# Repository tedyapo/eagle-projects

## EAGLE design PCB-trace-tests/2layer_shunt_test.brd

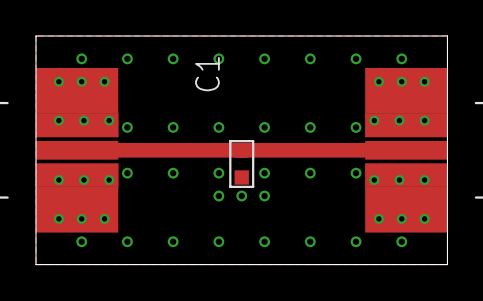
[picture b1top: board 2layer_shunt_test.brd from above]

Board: 2 copper layers, 22.9 x 12.7 mm, 3 parts (0 on the bottom side), 2 nets.

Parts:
C1: C0603
J1, J2: SMA_EDGE_LAUNCH_2L

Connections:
GND: C1.P$1, J1.BOTTOM_GND, J1.GND@1, J1.GND@2, J1.GND@3, J1.GND@4, J1.GND@5, J1.GND@6, J1.GND@7, J1.GND@8, J1.GND@11, J1.GND@12, J1.GND@14, J1.GND@15, J1.GND@16, J1.GND@17, J1.GND_PAD1, J1.GND_PAD2, J2.BOTTOM_GND, J2.GND@1, J2.GND@2, J2.GND@3, J2.GND@4, J2.GND@5, J2.GND@6, J2.GND@7, J2.GND@8, J2.GND@11, J2.GND@12, J2.GND@14, J2.GND@15, J2.GND@16, J2.GND@17, J2.GND_PAD1, J2.GND_PAD2
unnamed: C1.P$2, J1.CENTER@1, J2.CENTER@1

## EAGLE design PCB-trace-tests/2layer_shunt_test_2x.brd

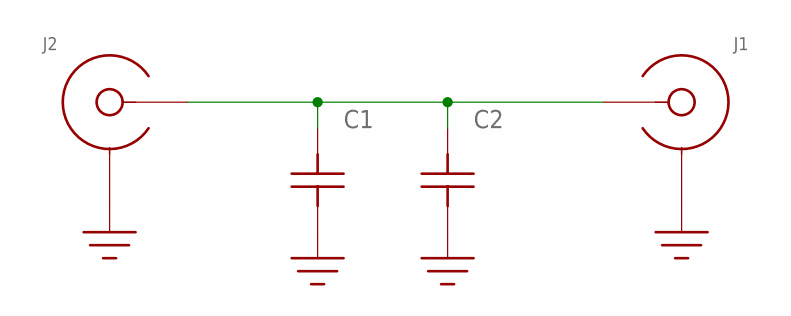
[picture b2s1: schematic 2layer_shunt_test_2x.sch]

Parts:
C1: C0603
C2: C; C0402
J1, J2: SMA_END_LAUNCH2L; SMA_EDGE_LAUNCH_2L

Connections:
GND: C1.P$1, C2.1, J1.BOTTOM_GND (SHIELD), J1.GND@1 (SHIELD), J1.GND@2 (SHIELD), J1.GND@3 (SHIELD), J1.GND@4 (SHIELD), J1.GND@5 (SHIELD), J1.GND@6 (SHIELD), J1.GND@7 (SHIELD), J1.GND@8 (SHIELD), J1.GND@11 (SHIELD), J1.GND@12 (SHIELD), J1.GND@14 (SHIELD), J1.GND@15 (SHIELD), J1.GND@16 (SHIELD), J1.GND@17 (SHIELD), J1.GND_PAD1 (SHIELD), J1.GND_PAD2 (SHIELD), J2.BOTTOM_GND (SHIELD), J2.GND@1 (SHIELD), J2.GND@2 (SHIELD), J2.GND@3 (SHIELD), J2.GND@4 (SHIELD), J2.GND@5 (SHIELD), J2.GND@6 (SHIELD), J2.GND@7 (SHIELD), J2.GND@8 (SHIELD), J2.GND@11 (SHIELD), J2.GND@12 (SHIELD), J2.GND@14 (SHIELD), J2.GND@15 (SHIELD), J2.GND@16 (SHIELD), J2.GND@17 (SHIELD), J2.GND_PAD1 (SHIELD), J2.GND_PAD2 (SHIELD)
unnamed: C1.P$2, C2.2, J1.CENTER@1 (CENTER), J2.CENTER@1 (CENTER)

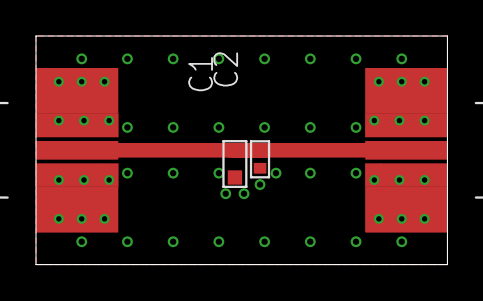
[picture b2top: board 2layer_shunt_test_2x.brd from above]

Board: 2 copper layers, 22.9 x 12.7 mm, 4 parts (0 on the bottom side), 2 nets.

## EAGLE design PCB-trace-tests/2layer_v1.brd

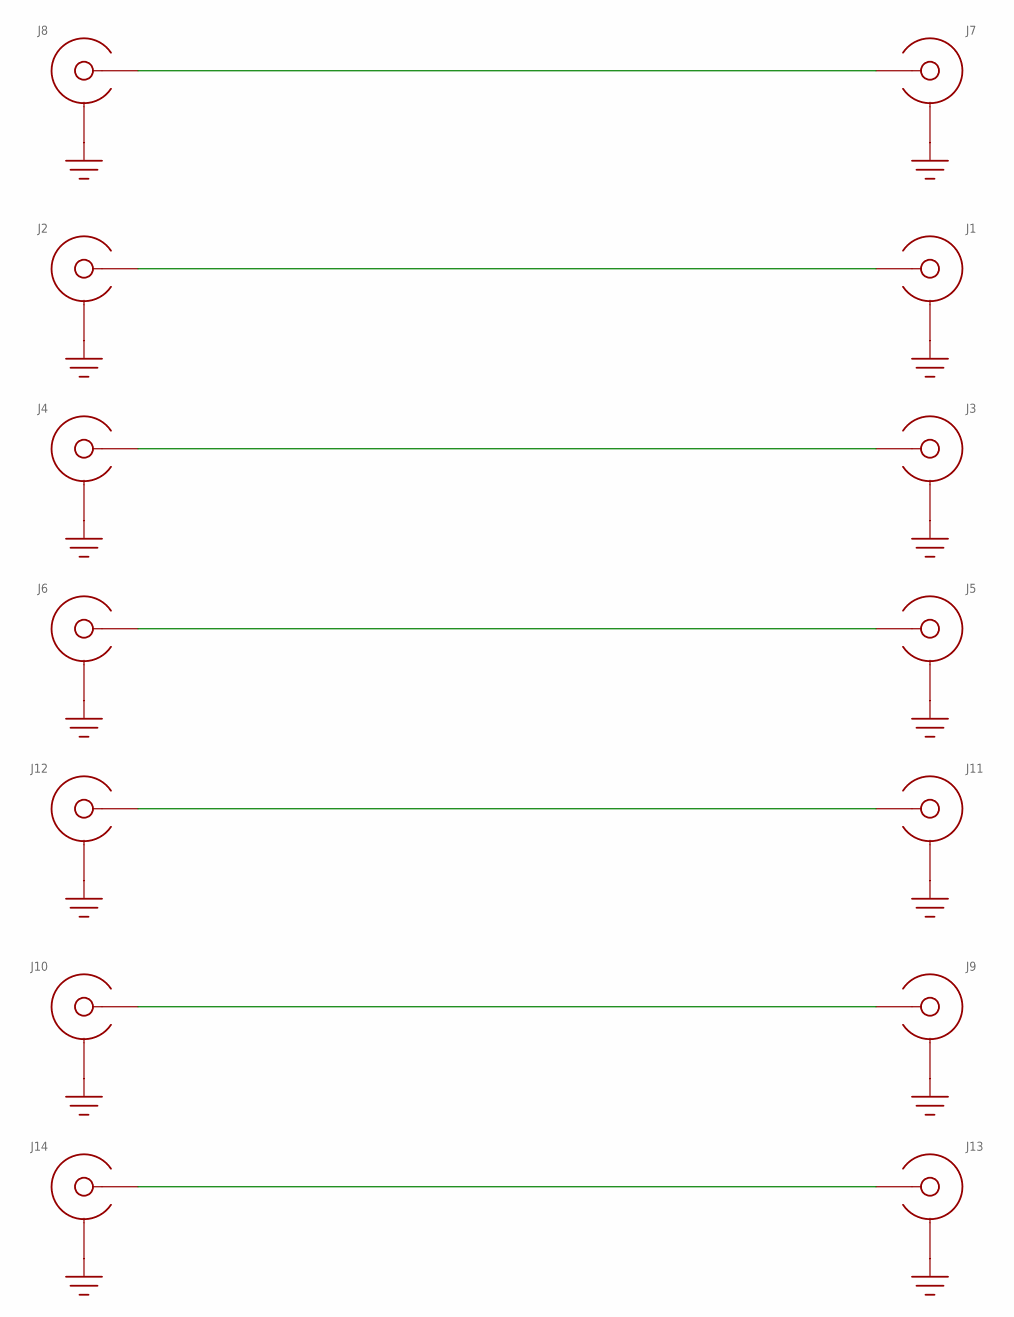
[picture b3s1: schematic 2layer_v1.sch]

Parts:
J1, J2, J3, J4, J5, J6, J7, J8, J9, J10, J11, J12, J13, J14: SMA_END_LAUNCH2L; SMA_EDGE_LAUNCH_2L

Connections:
GND: J1.BOTTOM_GND (SHIELD), J1.GND@1 (SHIELD), J1.GND@2 (SHIELD), J1.GND@3 (SHIELD), J1.GND@4 (SHIELD), J1.GND@5 (SHIELD), J1.GND@6 (SHIELD), J1.GND@7 (SHIELD), J1.GND@8 (SHIELD), J1.GND@11 (SHIELD), J1.GND@12 (SHIELD), J1.GND@14 (SHIELD), J1.GND@15 (SHIELD), J1.GND@16 (SHIELD), J1.GND@17 (SHIELD), J1.GND_PAD1 (SHIELD), J1.GND_PAD2 (SHIELD), J2.BOTTOM_GND (SHIELD), J2.GND@1 (SHIELD), J2.GND@2 (SHIELD), J2.GND@3 (SHIELD), J2.GND@4 (SHIELD), J2.GND@5 (SHIELD), J2.GND@6 (SHIELD), J2.GND@7 (SHIELD), J2.GND@8 (SHIELD), J2.GND@11 (SHIELD), J2.GND@12 (SHIELD), J2.GND@14 (SHIELD), J2.GND@15 (SHIELD), J2.GND@16 (SHIELD), J2.GND@17 (SHIELD), J2.GND_PAD1 (SHIELD), J2.GND_PAD2 (SHIELD), J3.BOTTOM_GND (SHIELD), J3.GND@1 (SHIELD), J3.GND@2 (SHIELD), J3.GND@3 (SHIELD), J3.GND@4 (SHIELD), J3.GND@5 (SHIELD), J3.GND@6 (SHIELD), J3.GND@7 (SHIELD), J3.GND@8 (SHIELD), J3.GND@11 (SHIELD), J3.GND@12 (SHIELD), J3.GND@14 (SHIELD), J3.GND@15 (SHIELD), J3.GND@16 (SHIELD), J3.GND@17 (SHIELD), J3.GND_PAD1 (SHIELD), J3.GND_PAD2 (SHIELD), J4.BOTTOM_GND (SHIELD), J4.GND@1 (SHIELD), J4.GND@2 (SHIELD), J4.GND@3 (SHIELD), J4.GND@4 (SHIELD), J4.GND@5 (SHIELD), J4.GND@6 (SHIELD), J4.GND@7 (SHIELD), J4.GND@8 (SHIELD), J4.GND@11 (SHIELD), J4.GND@12 (SHIELD), J4.GND@14 (SHIELD), J4.GND@15 (SHIELD), J4.GND@16 (SHIELD), J4.GND@17 (SHIELD), J4.GND_PAD1 (SHIELD), J4.GND_PAD2 (SHIELD), J5.BOTTOM_GND (SHIELD), J5.GND@1 (SHIELD), J5.GND@2 (SHIELD), J5.GND@3 (SHIELD), J5.GND@4 (SHIELD), J5.GND@5 (SHIELD), J5.GND@6 (SHIELD), J5.GND@7 (SHIELD), J5.GND@8 (SHIELD), J5.GND@11 (SHIELD), J5.GND@12 (SHIELD), J5.GND@14 (SHIELD), J5.GND@15 (SHIELD), J5.GND@16 (SHIELD), J5.GND@17 (SHIELD), J5.GND_PAD1 (SHIELD), J5.GND_PAD2 (SHIELD), J6.BOTTOM_GND (SHIELD), J6.GND@1 (SHIELD), J6.GND@2 (SHIELD), J6.GND@3 (SHIELD), J6.GND@4 (SHIELD), J6.GND@5 (SHIELD), J6.GND@6 (SHIELD), J6.GND@7 (SHIELD), J6.GND@8 (SHIELD), J6.GND@11 (SHIELD), J6.GND@12 (SHIELD), J6.GND@14 (SHIELD), J6.GND@15 (SHIELD), J6.GND@16 (SHIELD), J6.GND@17 (SHIELD), J6.GND_PAD1 (SHIELD), J6.GND_PAD2 (SHIELD), J7.BOTTOM_GND (SHIELD), J7.GND@1 (SHIELD), J7.GND@2 (SHIELD), J7.GND@3 (SHIELD), J7.GND@4 (SHIELD), J7.GND@5 (SHIELD), J7.GND@6 (SHIELD), J7.GND@7 (SHIELD), J7.GND@8 (SHIELD), J7.GND@11 (SHIELD), J7.GND@12 (SHIELD), J7.GND@14 (SHIELD), J7.GND@15 (SHIELD), J7.GND@16 (SHIELD), J7.GND@17 (SHIELD), J7.GND_PAD1 (SHIELD), J7.GND_PAD2 (SHIELD), J8.BOTTOM_GND (SHIELD), J8.GND@1 (SHIELD), J8.GND@2 (SHIELD), J8.GND@3 (SHIELD), J8.GND@4 (SHIELD), J8.GND@5 (SHIELD), J8.GND@6 (SHIELD), J8.GND@7 (SHIELD), J8.GND@8 (SHIELD), J8.GND@11 (SHIELD), J8.GND@12 (SHIELD), J8.GND@14 (SHIELD), J8.GND@15 (SHIELD), J8.GND@16 (SHIELD), J8.GND@17 (SHIELD), J8.GND_PAD1 (SHIELD), J8.GND_PAD2 (SHIELD), J9.BOTTOM_GND (SHIELD), J9.GND@1 (SHIELD), J9.GND@2 (SHIELD), J9.GND@3 (SHIELD), J9.GND@4 (SHIELD), J9.GND@5 (SHIELD), J9.GND@6 (SHIELD), J9.GND@7 (SHIELD), J9.GND@8 (SHIELD), J9.GND@11 (SHIELD), J9.GND@12 (SHIELD), J9.GND@14 (SHIELD), J9.GND@15 (SHIELD), J9.GND@16 (SHIELD), J9.GND@17 (SHIELD), J9.GND_PAD1 (SHIELD), J9.GND_PAD2 (SHIELD), J10.BOTTOM_GND (SHIELD), J10.GND@1 (SHIELD), J10.GND@2 (SHIELD), J10.GND@3 (SHIELD), J10.GND@4 (SHIELD), J10.GND@5 (SHIELD), J10.GND@6 (SHIELD), J10.GND@7 (SHIELD), J10.GND@8 (SHIELD), J10.GND@11 (SHIELD), J10.GND@12 (SHIELD), J10.GND@14 (SHIELD), J10.GND@15 (SHIELD), J10.GND@16 (SHIELD), J10.GND@17 (SHIELD), J10.GND_PAD1 (SHIELD), J10.GND_PAD2 (SHIELD), J11.BOTTOM_GND (SHIELD), J11.GND@1 (SHIELD), J11.GND@2 (SHIELD), J11.GND@3 (SHIELD), J11.GND@4 (SHIELD), J11.GND@5 (SHIELD), J11.GND@6 (SHIELD), J11.GND@7 (SHIELD), J11.GND@8 (SHIELD), J11.GND@11 (SHIELD), J11.GND@12 (SHIELD), J11.GND@14 (SHIELD), J11.GND@15 (SHIELD), J11.GND@16 (SHIELD), J11.GND@17 (SHIELD), J11.GND_PAD1 (SHIELD), J11.GND_PAD2 (SHIELD), J12.BOTTOM_GND (SHIELD), J12.GND@1 (SHIELD), J12.GND@2 (SHIELD), J12.GND@3 (SHIELD), J12.GND@4 (SHIELD), J12.GND@5 (SHIELD), J12.GND@6 (SHIELD), J12.GND@7 (SHIELD), J12.GND@8 (SHIELD), J12.GND@11 (SHIELD), J12.GND@12 (SHIELD), J12.GND@14 (SHIELD), J12.GND@15 (SHIELD), J12.GND@16 (SHIELD), J12.GND@17 (SHIELD), J12.GND_PAD1 (SHIELD), J12.GND_PAD2 (SHIELD), J13.BOTTOM_GND (SHIELD), J13.GND@1 (SHIELD), J13.GND@2 (SHIELD), J13.GND@3 (SHIELD), J13.GND@4 (SHIELD), J13.GND@5 (SHIELD), J13.GND@6 (SHIELD), J13.GND@7 (SHIELD), J13.GND@8 (SHIELD), J13.GND@11 (SHIELD), J13.GND@12 (SHIELD), J13.GND@14 (SHIELD), J13.GND@15 (SHIELD), J13.GND@16 (SHIELD), J13.GND@17 (SHIELD), J13.GND_PAD1 (SHIELD), J13.GND_PAD2 (SHIELD), J14.BOTTOM_GND (SHIELD), J14.GND@1 (SHIELD), J14.GND@2 (SHIELD), J14.GND@3 (SHIELD), J14.GND@4 (SHIELD), J14.GND@5 (SHIELD), J14.GND@6 (SHIELD), J14.GND@7 (SHIELD), J14.GND@8 (SHIELD), J14.GND@11 (SHIELD), J14.GND@12 (SHIELD), J14.GND@14 (SHIELD), J14.GND@15 (SHIELD), J14.GND@16 (SHIELD), J14.GND@17 (SHIELD), J14.GND_PAD1 (SHIELD), J14.GND_PAD2 (SHIELD)
unnamed: J1.CENTER@1 (CENTER), J2.CENTER@1 (CENTER)
unnamed: J3.CENTER@1 (CENTER), J4.CENTER@1 (CENTER)
unnamed: J5.CENTER@1 (CENTER), J6.CENTER@1 (CENTER)
unnamed: J7.CENTER@1 (CENTER), J8.CENTER@1 (CENTER)
unnamed: J9.CENTER@1 (CENTER), J10.CENTER@1 (CENTER)
unnamed: J11.CENTER@1 (CENTER), J12.CENTER@1 (CENTER)
unnamed: J13.CENTER@1 (CENTER), J14.CENTER@1 (CENTER)

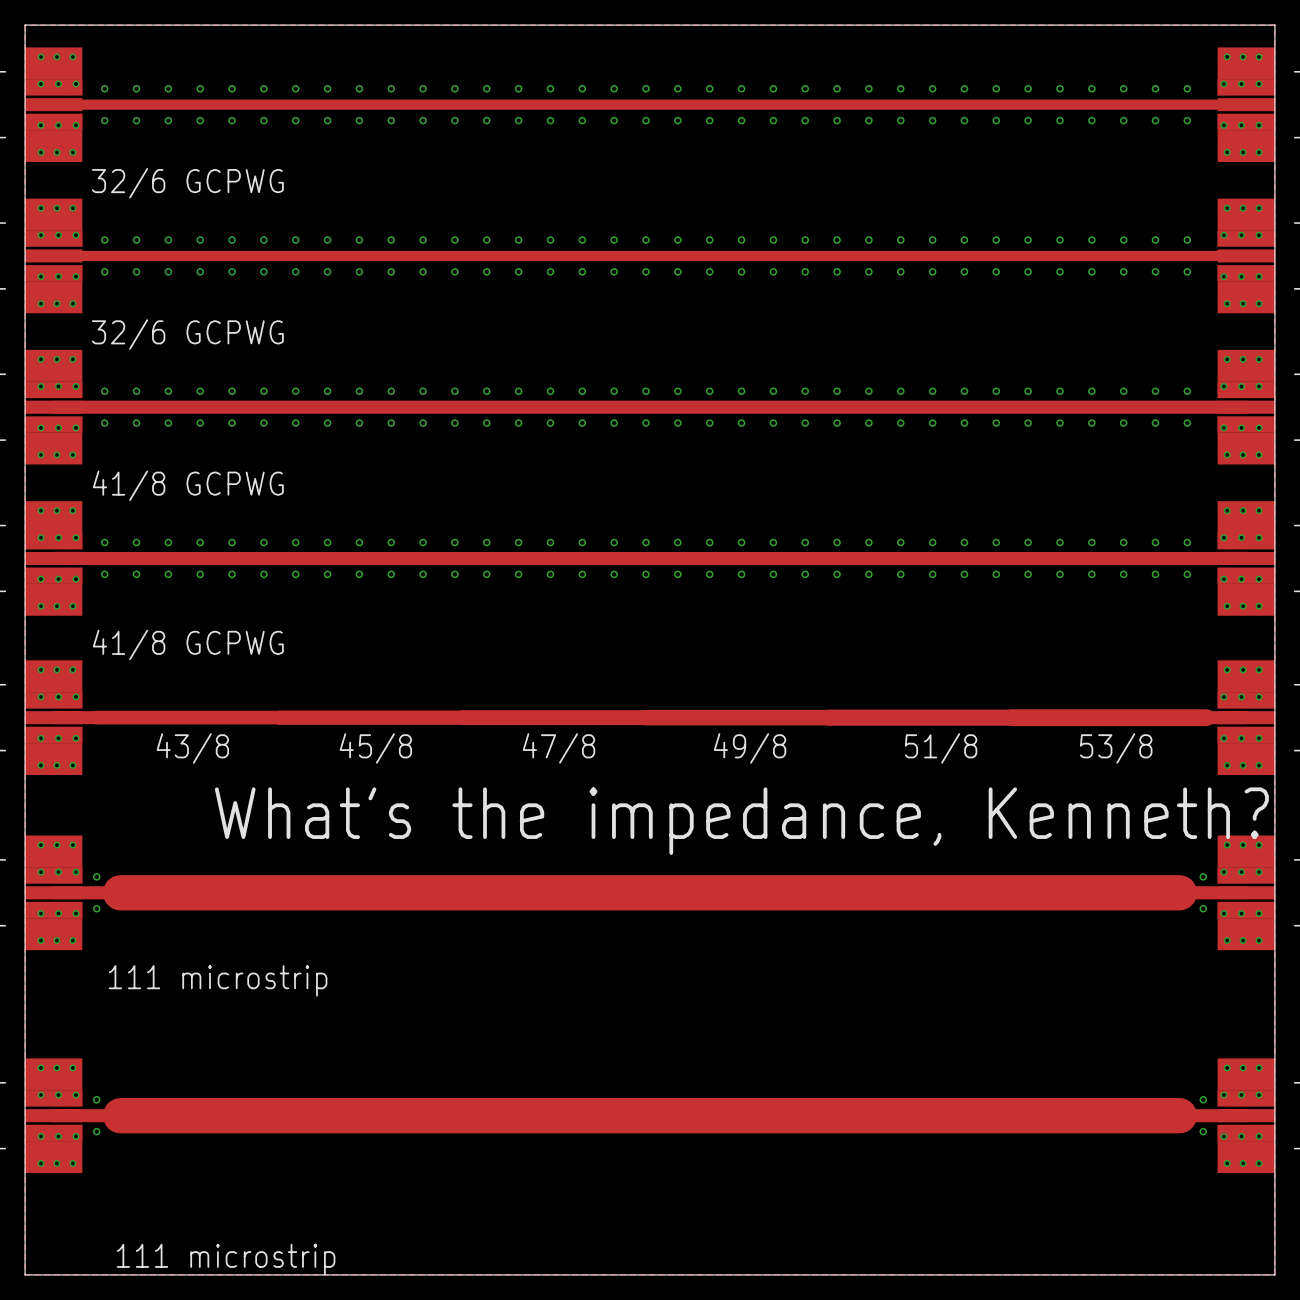
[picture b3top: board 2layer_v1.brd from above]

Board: 2 copper layers, 99.7 x 99.7 mm, 14 parts (0 on the bottom side), 8 nets.

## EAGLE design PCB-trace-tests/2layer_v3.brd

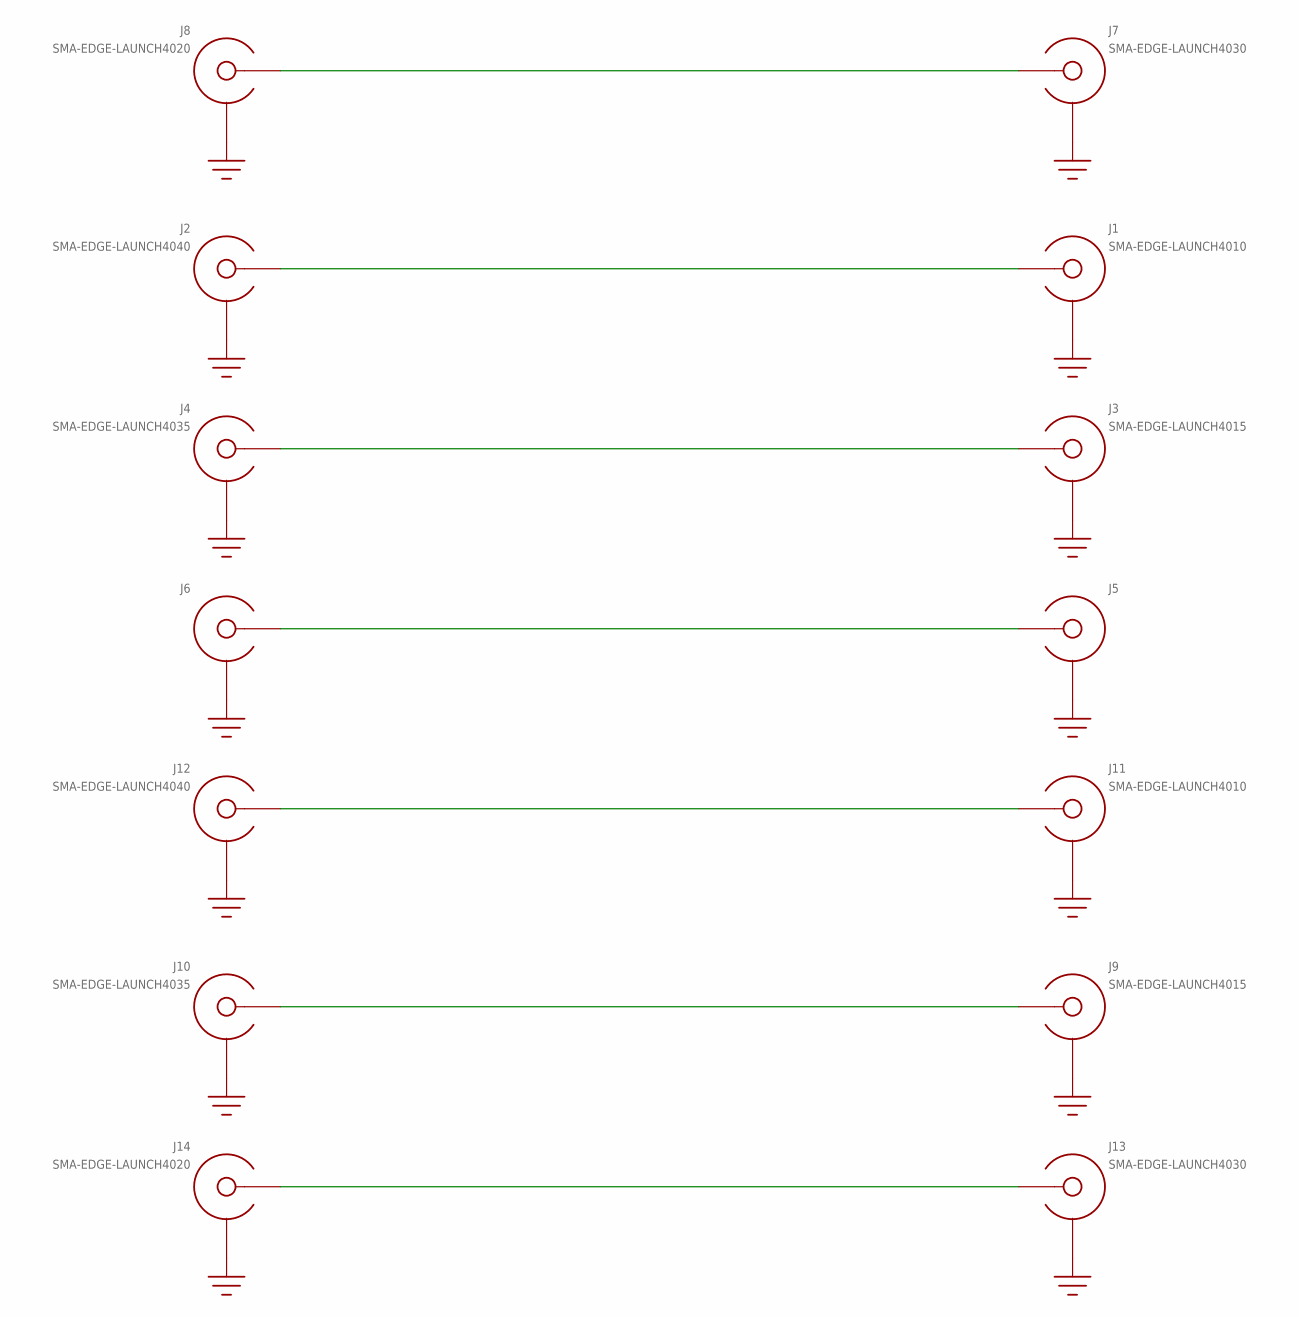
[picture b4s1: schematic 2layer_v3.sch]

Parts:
J1: SMA-EDGE-LAUNCH4010; SMA_EDGE_LAUNCH_2L_4020_CUT_PIN
J2: SMA-EDGE-LAUNCH4040; SMA_EDGE_LAUNCH_2L_4020_TAPER
J3: SMA-EDGE-LAUNCH4015; SMA_EDGE_LAUNCH_2L_4020_CUT_PIN
J4: SMA-EDGE-LAUNCH4035; SMA_EDGE_LAUNCH_2L_4020_TAPER
J5: SMA-EDGE-LAUNCHCUT-PIN; SMA_EDGE_LAUNCH_2L_4020_CUT_PIN
J6: SMA-EDGE-LAUNCH4020_TAPER; SMA_EDGE_LAUNCH_2L_4020_TAPER
J7: SMA-EDGE-LAUNCH4030; SMA_EDGE_LAUNCH_2L_4020_CUT_PIN
J8: SMA-EDGE-LAUNCH4020; SMA_EDGE_LAUNCH_2L_4020_TAPER
J9: SMA-EDGE-LAUNCH4015; SMA_EDGE_LAUNCH_2L_4020_TAPER
J10: SMA-EDGE-LAUNCH4035; SMA_EDGE_LAUNCH_2L_4020_CUT_PIN
J11: SMA-EDGE-LAUNCH4010; SMA_EDGE_LAUNCH_2L_4020_TAPER
J12: SMA-EDGE-LAUNCH4040; SMA_EDGE_LAUNCH_2L_4020_CUT_PIN
J13: SMA-EDGE-LAUNCH4030; SMA_EDGE_LAUNCH_2L_4020_TAPER
J14: SMA-EDGE-LAUNCH4020; SMA_EDGE_LAUNCH_2L_4020_CUT_PIN

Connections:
GND: J1.BOTTOM_GND (SHIELD), J1.GND@1 (SHIELD), J1.GND@2 (SHIELD), J1.GND@3 (SHIELD), J1.GND@4 (SHIELD), J1.GND@5 (SHIELD), J1.GND@6 (SHIELD), J1.GND@7 (SHIELD), J1.GND@8 (SHIELD), J1.GND@14 (SHIELD), J1.GND@15 (SHIELD), J1.GND@16 (SHIELD), J1.GND@17 (SHIELD), J1.GND_PAD1 (SHIELD), J1.GND_PAD2 (SHIELD), J2.BOTTOM_GND (SHIELD), J2.GND@1 (SHIELD), J2.GND@2 (SHIELD), J2.GND@3 (SHIELD), J2.GND@4 (SHIELD), J2.GND@5 (SHIELD), J2.GND@6 (SHIELD), J2.GND@7 (SHIELD), J2.GND@8 (SHIELD), J2.GND@14 (SHIELD), J2.GND@15 (SHIELD), J2.GND@16 (SHIELD), J2.GND@17 (SHIELD), J2.GND_PAD1 (SHIELD), J2.GND_PAD2 (SHIELD), J2.P$1 (SHIELD), J2.P$2 (SHIELD), J3.BOTTOM_GND (SHIELD), J3.GND@1 (SHIELD), J3.GND@2 (SHIELD), J3.GND@3 (SHIELD), J3.GND@4 (SHIELD), J3.GND@5 (SHIELD), J3.GND@6 (SHIELD), J3.GND@7 (SHIELD), J3.GND@8 (SHIELD), J3.GND@14 (SHIELD), J3.GND@15 (SHIELD), J3.GND@16 (SHIELD), J3.GND@17 (SHIELD), J3.GND_PAD1 (SHIELD), J3.GND_PAD2 (SHIELD), J4.BOTTOM_GND (SHIELD), J4.GND@1 (SHIELD), J4.GND@2 (SHIELD), J4.GND@3 (SHIELD), J4.GND@4 (SHIELD), J4.GND@5 (SHIELD), J4.GND@6 (SHIELD), J4.GND@7 (SHIELD), J4.GND@8 (SHIELD), J4.GND@14 (SHIELD), J4.GND@15 (SHIELD), J4.GND@16 (SHIELD), J4.GND@17 (SHIELD), J4.GND_PAD1 (SHIELD), J4.GND_PAD2 (SHIELD), J4.P$1 (SHIELD), J4.P$2 (SHIELD), J5.BOTTOM_GND (SHIELD), J5.GND@1 (SHIELD), J5.GND@2 (SHIELD), J5.GND@3 (SHIELD), J5.GND@4 (SHIELD), J5.GND@5 (SHIELD), J5.GND@6 (SHIELD), J5.GND@7 (SHIELD), J5.GND@8 (SHIELD), J5.GND@14 (SHIELD), J5.GND@15 (SHIELD), J5.GND@16 (SHIELD), J5.GND@17 (SHIELD), J5.GND_PAD1 (SHIELD), J5.GND_PAD2 (SHIELD), J6.BOTTOM_GND (SHIELD), J6.GND@1 (SHIELD), J6.GND@2 (SHIELD), J6.GND@3 (SHIELD), J6.GND@4 (SHIELD), J6.GND@5 (SHIELD), J6.GND@6 (SHIELD), J6.GND@7 (SHIELD), J6.GND@8 (SHIELD), J6.GND@14 (SHIELD), J6.GND@15 (SHIELD), J6.GND@16 (SHIELD), J6.GND@17 (SHIELD), J6.GND_PAD1 (SHIELD), J6.GND_PAD2 (SHIELD), J6.P$1 (SHIELD), J6.P$2 (SHIELD), J7.BOTTOM_GND (SHIELD), J7.GND@1 (SHIELD), J7.GND@2 (SHIELD), J7.GND@3 (SHIELD), J7.GND@4 (SHIELD), J7.GND@5 (SHIELD), J7.GND@6 (SHIELD), J7.GND@7 (SHIELD), J7.GND@8 (SHIELD), J7.GND@14 (SHIELD), J7.GND@15 (SHIELD), J7.GND@16 (SHIELD), J7.GND@17 (SHIELD), J7.GND_PAD1 (SHIELD), J7.GND_PAD2 (SHIELD), J8.BOTTOM_GND (SHIELD), J8.GND@1 (SHIELD), J8.GND@2 (SHIELD), J8.GND@3 (SHIELD), J8.GND@4 (SHIELD), J8.GND@5 (SHIELD), J8.GND@6 (SHIELD), J8.GND@7 (SHIELD), J8.GND@8 (SHIELD), J8.GND@14 (SHIELD), J8.GND@15 (SHIELD), J8.GND@16 (SHIELD), J8.GND@17 (SHIELD), J8.GND_PAD1 (SHIELD), J8.GND_PAD2 (SHIELD), J8.P$1 (SHIELD), J8.P$2 (SHIELD), J9.BOTTOM_GND (SHIELD), J9.GND@1 (SHIELD), J9.GND@2 (SHIELD), J9.GND@3 (SHIELD), J9.GND@4 (SHIELD), J9.GND@5 (SHIELD), J9.GND@6 (SHIELD), J9.GND@7 (SHIELD), J9.GND@8 (SHIELD), J9.GND@14 (SHIELD), J9.GND@15 (SHIELD), J9.GND@16 (SHIELD), J9.GND@17 (SHIELD), J9.GND_PAD1 (SHIELD), J9.GND_PAD2 (SHIELD), J9.P$1 (SHIELD), J9.P$2 (SHIELD), J10.BOTTOM_GND (SHIELD), J10.GND@1 (SHIELD), J10.GND@2 (SHIELD), J10.GND@3 (SHIELD), J10.GND@4 (SHIELD), J10.GND@5 (SHIELD), J10.GND@6 (SHIELD), J10.GND@7 (SHIELD), J10.GND@8 (SHIELD), J10.GND@14 (SHIELD), J10.GND@15 (SHIELD), J10.GND@16 (SHIELD), J10.GND@17 (SHIELD), J10.GND_PAD1 (SHIELD), J10.GND_PAD2 (SHIELD), J11.BOTTOM_GND (SHIELD), J11.GND@1 (SHIELD), J11.GND@2 (SHIELD), J11.GND@3 (SHIELD), J11.GND@4 (SHIELD), J11.GND@5 (SHIELD), J11.GND@6 (SHIELD), J11.GND@7 (SHIELD), J11.GND@8 (SHIELD), J11.GND@14 (SHIELD), J11.GND@15 (SHIELD), J11.GND@16 (SHIELD), J11.GND@17 (SHIELD), J11.GND_PAD1 (SHIELD), J11.GND_PAD2 (SHIELD), J11.P$1 (SHIELD), J11.P$2 (SHIELD), J12.BOTTOM_GND (SHIELD), J12.GND@1 (SHIELD), J12.GND@2 (SHIELD), J12.GND@3 (SHIELD), J12.GND@4 (SHIELD), J12.GND@5 (SHIELD), J12.GND@6 (SHIELD), J12.GND@7 (SHIELD), J12.GND@8 (SHIELD), J12.GND@14 (SHIELD), J12.GND@15 (SHIELD), J12.GND@16 (SHIELD), J12.GND@17 (SHIELD), J12.GND_PAD1 (SHIELD), J12.GND_PAD2 (SHIELD), J13.BOTTOM_GND (SHIELD), J13.GND@1 (SHIELD), J13.GND@2 (SHIELD), J13.GND@3 (SHIELD), J13.GND@4 (SHIELD), J13.GND@5 (SHIELD), J13.GND@6 (SHIELD), J13.GND@7 (SHIELD), J13.GND@8 (SHIELD), J13.GND@14 (SHIELD), J13.GND@15 (SHIELD), J13.GND@16 (SHIELD), J13.GND@17 (SHIELD), J13.GND_PAD1 (SHIELD), J13.GND_PAD2 (SHIELD), J13.P$1 (SHIELD), J13.P$2 (SHIELD), J14.BOTTOM_GND (SHIELD), J14.GND@1 (SHIELD), J14.GND@2 (SHIELD), J14.GND@3 (SHIELD), J14.GND@4 (SHIELD), J14.GND@5 (SHIELD), J14.GND@6 (SHIELD), J14.GND@7 (SHIELD), J14.GND@8 (SHIELD), J14.GND@14 (SHIELD), J14.GND@15 (SHIELD), J14.GND@16 (SHIELD), J14.GND@17 (SHIELD), J14.GND_PAD1 (SHIELD), J14.GND_PAD2 (SHIELD)
unnamed: J1.CENTER@1 (CENTER), J1.CENTER@3 (CENTER), J2.CENTER@1 (CENTER)
unnamed: J3.CENTER@1 (CENTER), J3.CENTER@3 (CENTER), J4.CENTER@1 (CENTER)
unnamed: J5.CENTER@1 (CENTER), J5.CENTER@3 (CENTER), J6.CENTER@1 (CENTER)
unnamed: J7.CENTER@1 (CENTER), J7.CENTER@3 (CENTER), J8.CENTER@1 (CENTER)
unnamed: J9.CENTER@1 (CENTER), J10.CENTER@1 (CENTER), J10.CENTER@3 (CENTER)
unnamed: J11.CENTER@1 (CENTER), J12.CENTER@1 (CENTER), J12.CENTER@3 (CENTER)
unnamed: J13.CENTER@1 (CENTER), J14.CENTER@1 (CENTER), J14.CENTER@3 (CENTER)

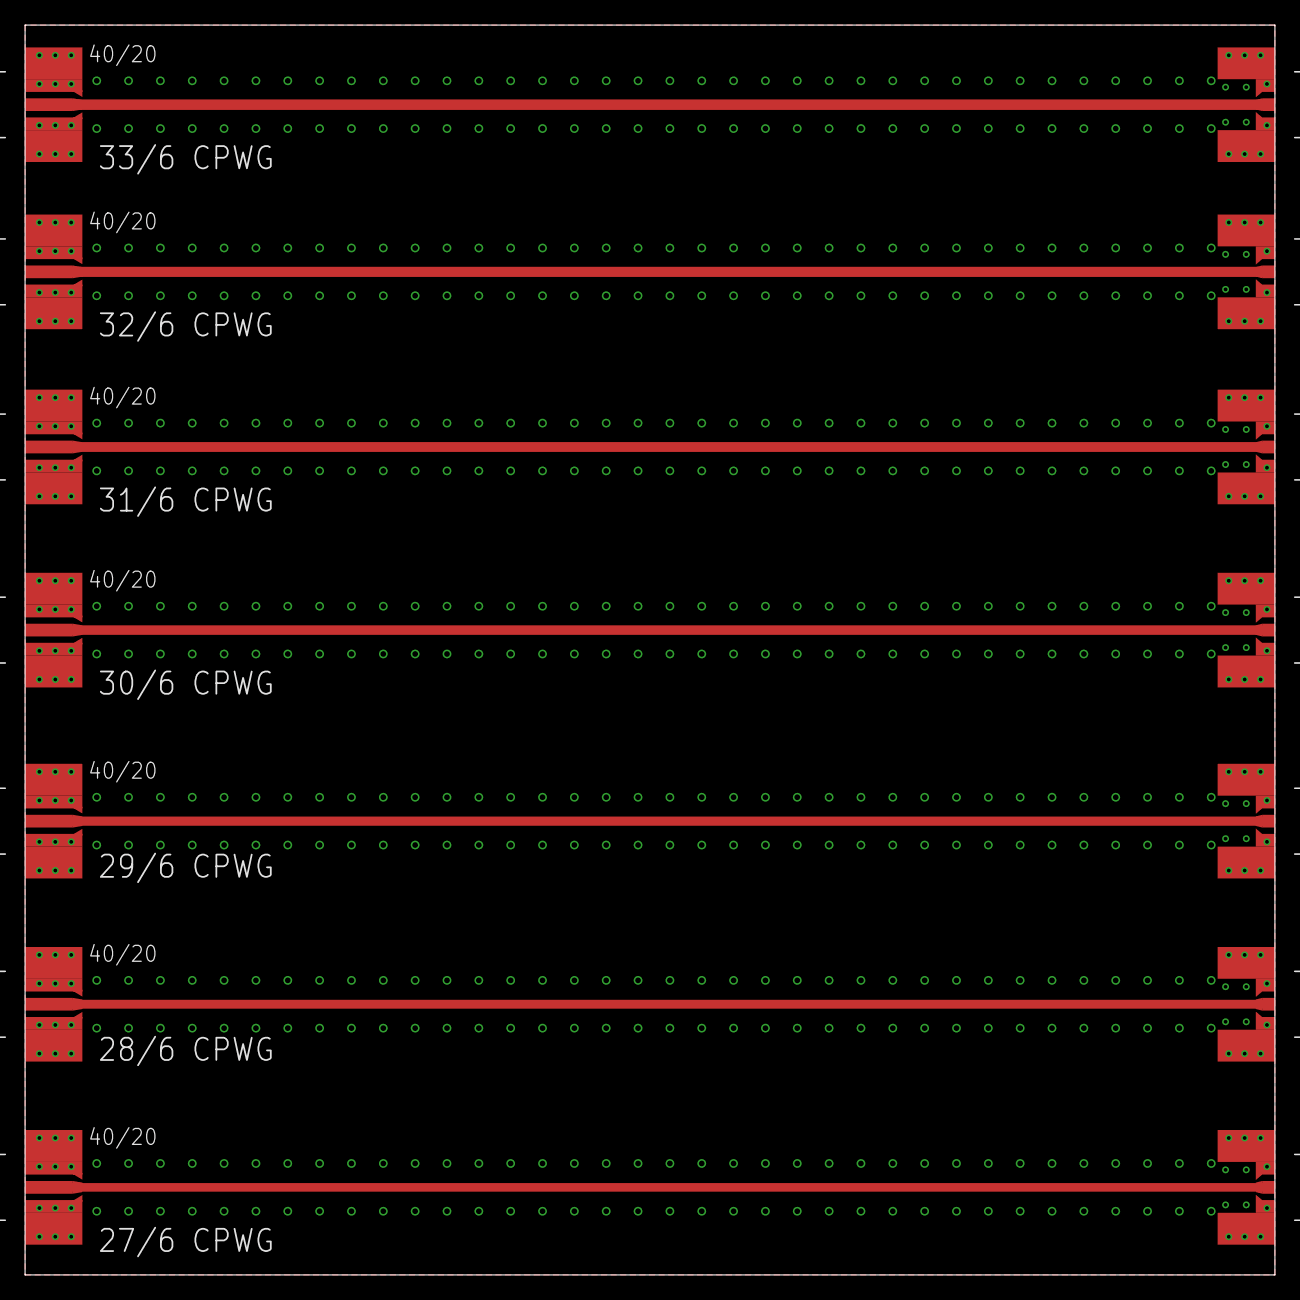
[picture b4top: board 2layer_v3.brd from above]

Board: 2 copper layers, 99.7 x 99.7 mm, 14 parts (0 on the bottom side), 8 nets.

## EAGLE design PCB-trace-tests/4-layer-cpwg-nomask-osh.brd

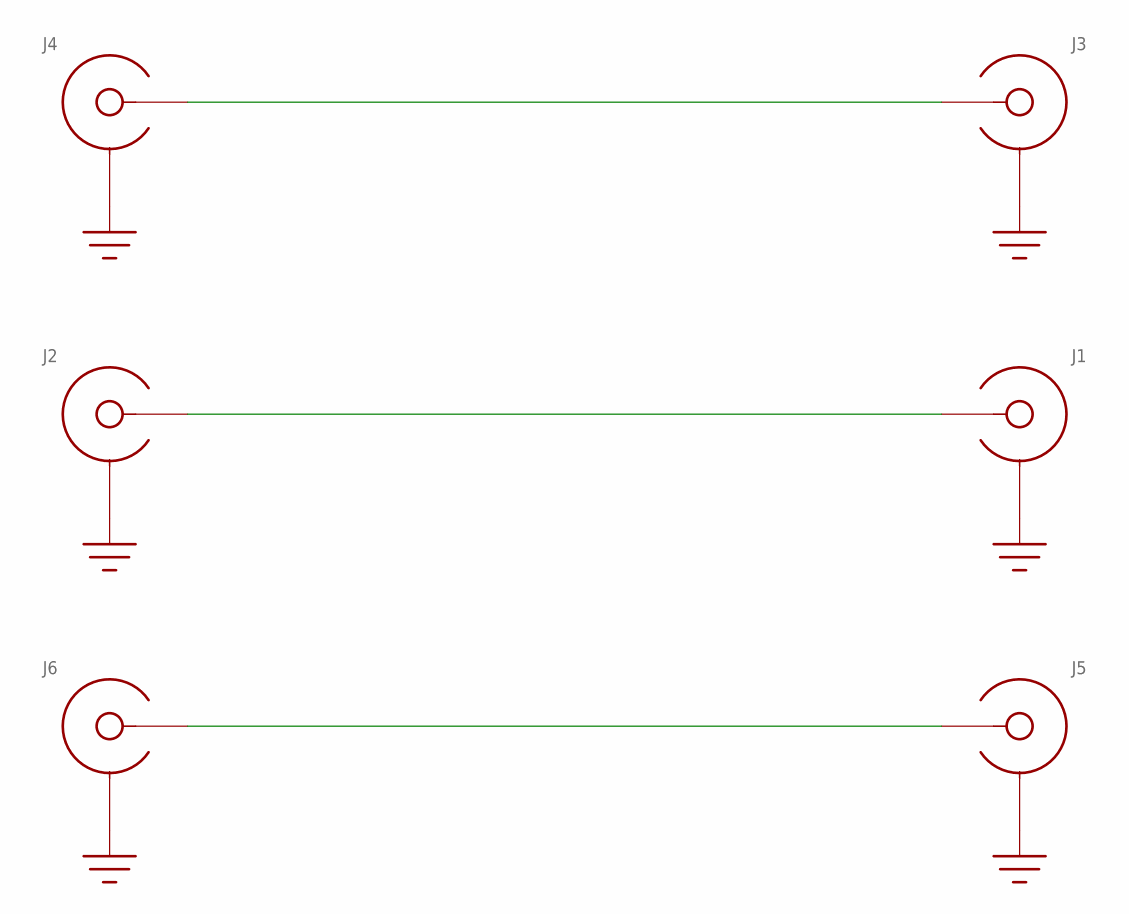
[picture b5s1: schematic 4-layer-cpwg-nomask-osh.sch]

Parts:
J1, J2, J3, J4, J5, J6: SMA-EDGE-LAUNCH4L-4020-TAPER-FIXED; SMA_EDGE_LAUNCH_4L_4020_TAPER_FIXED

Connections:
GND: J1.BOTTOM_GND (SHIELD), J1.GND@1 (SHIELD), J1.GND@2 (SHIELD), J1.GND@3 (SHIELD), J1.GND@4 (SHIELD), J1.GND@5 (SHIELD), J1.GND@6 (SHIELD), J1.GND@7 (SHIELD), J1.GND@8 (SHIELD), J1.GND@14 (SHIELD), J1.GND@15 (SHIELD), J1.GND@16 (SHIELD), J1.GND@17 (SHIELD), J1.GND_PAD1 (SHIELD), J1.GND_PAD2 (SHIELD), J1.P$1 (SHIELD), J1.P$2 (SHIELD), J2.BOTTOM_GND (SHIELD), J2.GND@1 (SHIELD), J2.GND@2 (SHIELD), J2.GND@3 (SHIELD), J2.GND@4 (SHIELD), J2.GND@5 (SHIELD), J2.GND@6 (SHIELD), J2.GND@7 (SHIELD), J2.GND@8 (SHIELD), J2.GND@14 (SHIELD), J2.GND@15 (SHIELD), J2.GND@16 (SHIELD), J2.GND@17 (SHIELD), J2.GND_PAD1 (SHIELD), J2.GND_PAD2 (SHIELD), J2.P$1 (SHIELD), J2.P$2 (SHIELD), J3.BOTTOM_GND (SHIELD), J3.GND@1 (SHIELD), J3.GND@2 (SHIELD), J3.GND@3 (SHIELD), J3.GND@4 (SHIELD), J3.GND@5 (SHIELD), J3.GND@6 (SHIELD), J3.GND@7 (SHIELD), J3.GND@8 (SHIELD), J3.GND@14 (SHIELD), J3.GND@15 (SHIELD), J3.GND@16 (SHIELD), J3.GND@17 (SHIELD), J3.GND_PAD1 (SHIELD), J3.GND_PAD2 (SHIELD), J3.P$1 (SHIELD), J3.P$2 (SHIELD), J4.BOTTOM_GND (SHIELD), J4.GND@1 (SHIELD), J4.GND@2 (SHIELD), J4.GND@3 (SHIELD), J4.GND@4 (SHIELD), J4.GND@5 (SHIELD), J4.GND@6 (SHIELD), J4.GND@7 (SHIELD), J4.GND@8 (SHIELD), J4.GND@14 (SHIELD), J4.GND@15 (SHIELD), J4.GND@16 (SHIELD), J4.GND@17 (SHIELD), J4.GND_PAD1 (SHIELD), J4.GND_PAD2 (SHIELD), J4.P$1 (SHIELD), J4.P$2 (SHIELD), J5.BOTTOM_GND (SHIELD), J5.GND@1 (SHIELD), J5.GND@2 (SHIELD), J5.GND@3 (SHIELD), J5.GND@4 (SHIELD), J5.GND@5 (SHIELD), J5.GND@6 (SHIELD), J5.GND@7 (SHIELD), J5.GND@8 (SHIELD), J5.GND@14 (SHIELD), J5.GND@15 (SHIELD), J5.GND@16 (SHIELD), J5.GND@17 (SHIELD), J5.GND_PAD1 (SHIELD), J5.GND_PAD2 (SHIELD), J5.P$1 (SHIELD), J5.P$2 (SHIELD), J6.BOTTOM_GND (SHIELD), J6.GND@1 (SHIELD), J6.GND@2 (SHIELD), J6.GND@3 (SHIELD), J6.GND@4 (SHIELD), J6.GND@5 (SHIELD), J6.GND@6 (SHIELD), J6.GND@7 (SHIELD), J6.GND@8 (SHIELD), J6.GND@14 (SHIELD), J6.GND@15 (SHIELD), J6.GND@16 (SHIELD), J6.GND@17 (SHIELD), J6.GND_PAD1 (SHIELD), J6.GND_PAD2 (SHIELD), J6.P$1 (SHIELD), J6.P$2 (SHIELD)
unnamed: J1.CENTER@1 (CENTER), J1.P$3 (CENTER), J2.CENTER@1 (CENTER), J2.P$3 (CENTER)
unnamed: J3.CENTER@1 (CENTER), J3.P$3 (CENTER), J4.CENTER@1 (CENTER), J4.P$3 (CENTER)
unnamed: J5.CENTER@1 (CENTER), J5.P$3 (CENTER), J6.CENTER@1 (CENTER), J6.P$3 (CENTER)

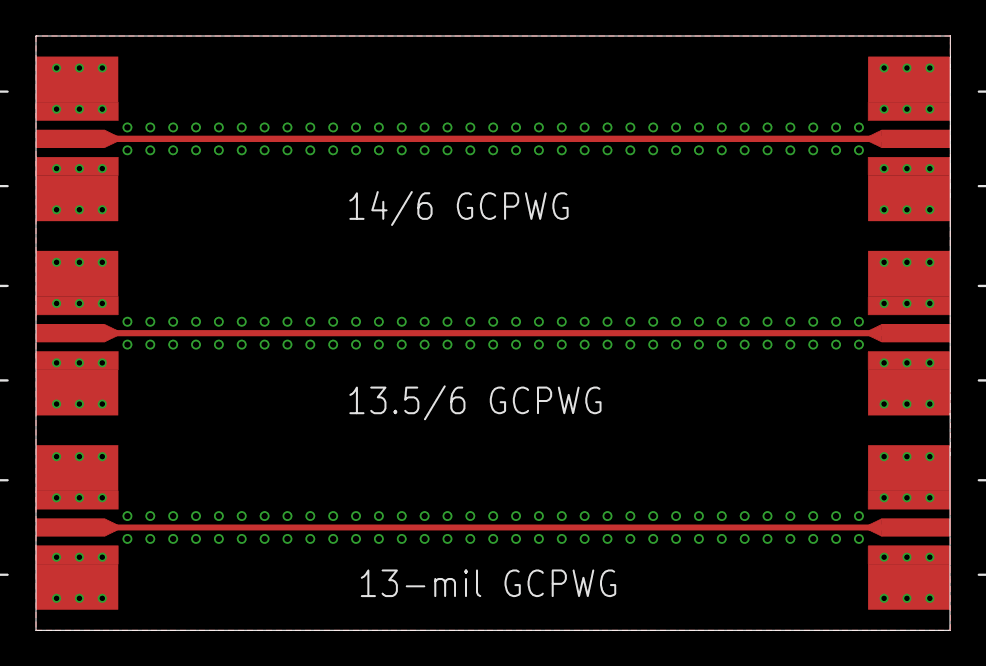
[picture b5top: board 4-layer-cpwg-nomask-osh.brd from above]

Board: 4 copper layers, 50.8 x 33.0 mm, 6 parts (0 on the bottom side), 4 nets.
